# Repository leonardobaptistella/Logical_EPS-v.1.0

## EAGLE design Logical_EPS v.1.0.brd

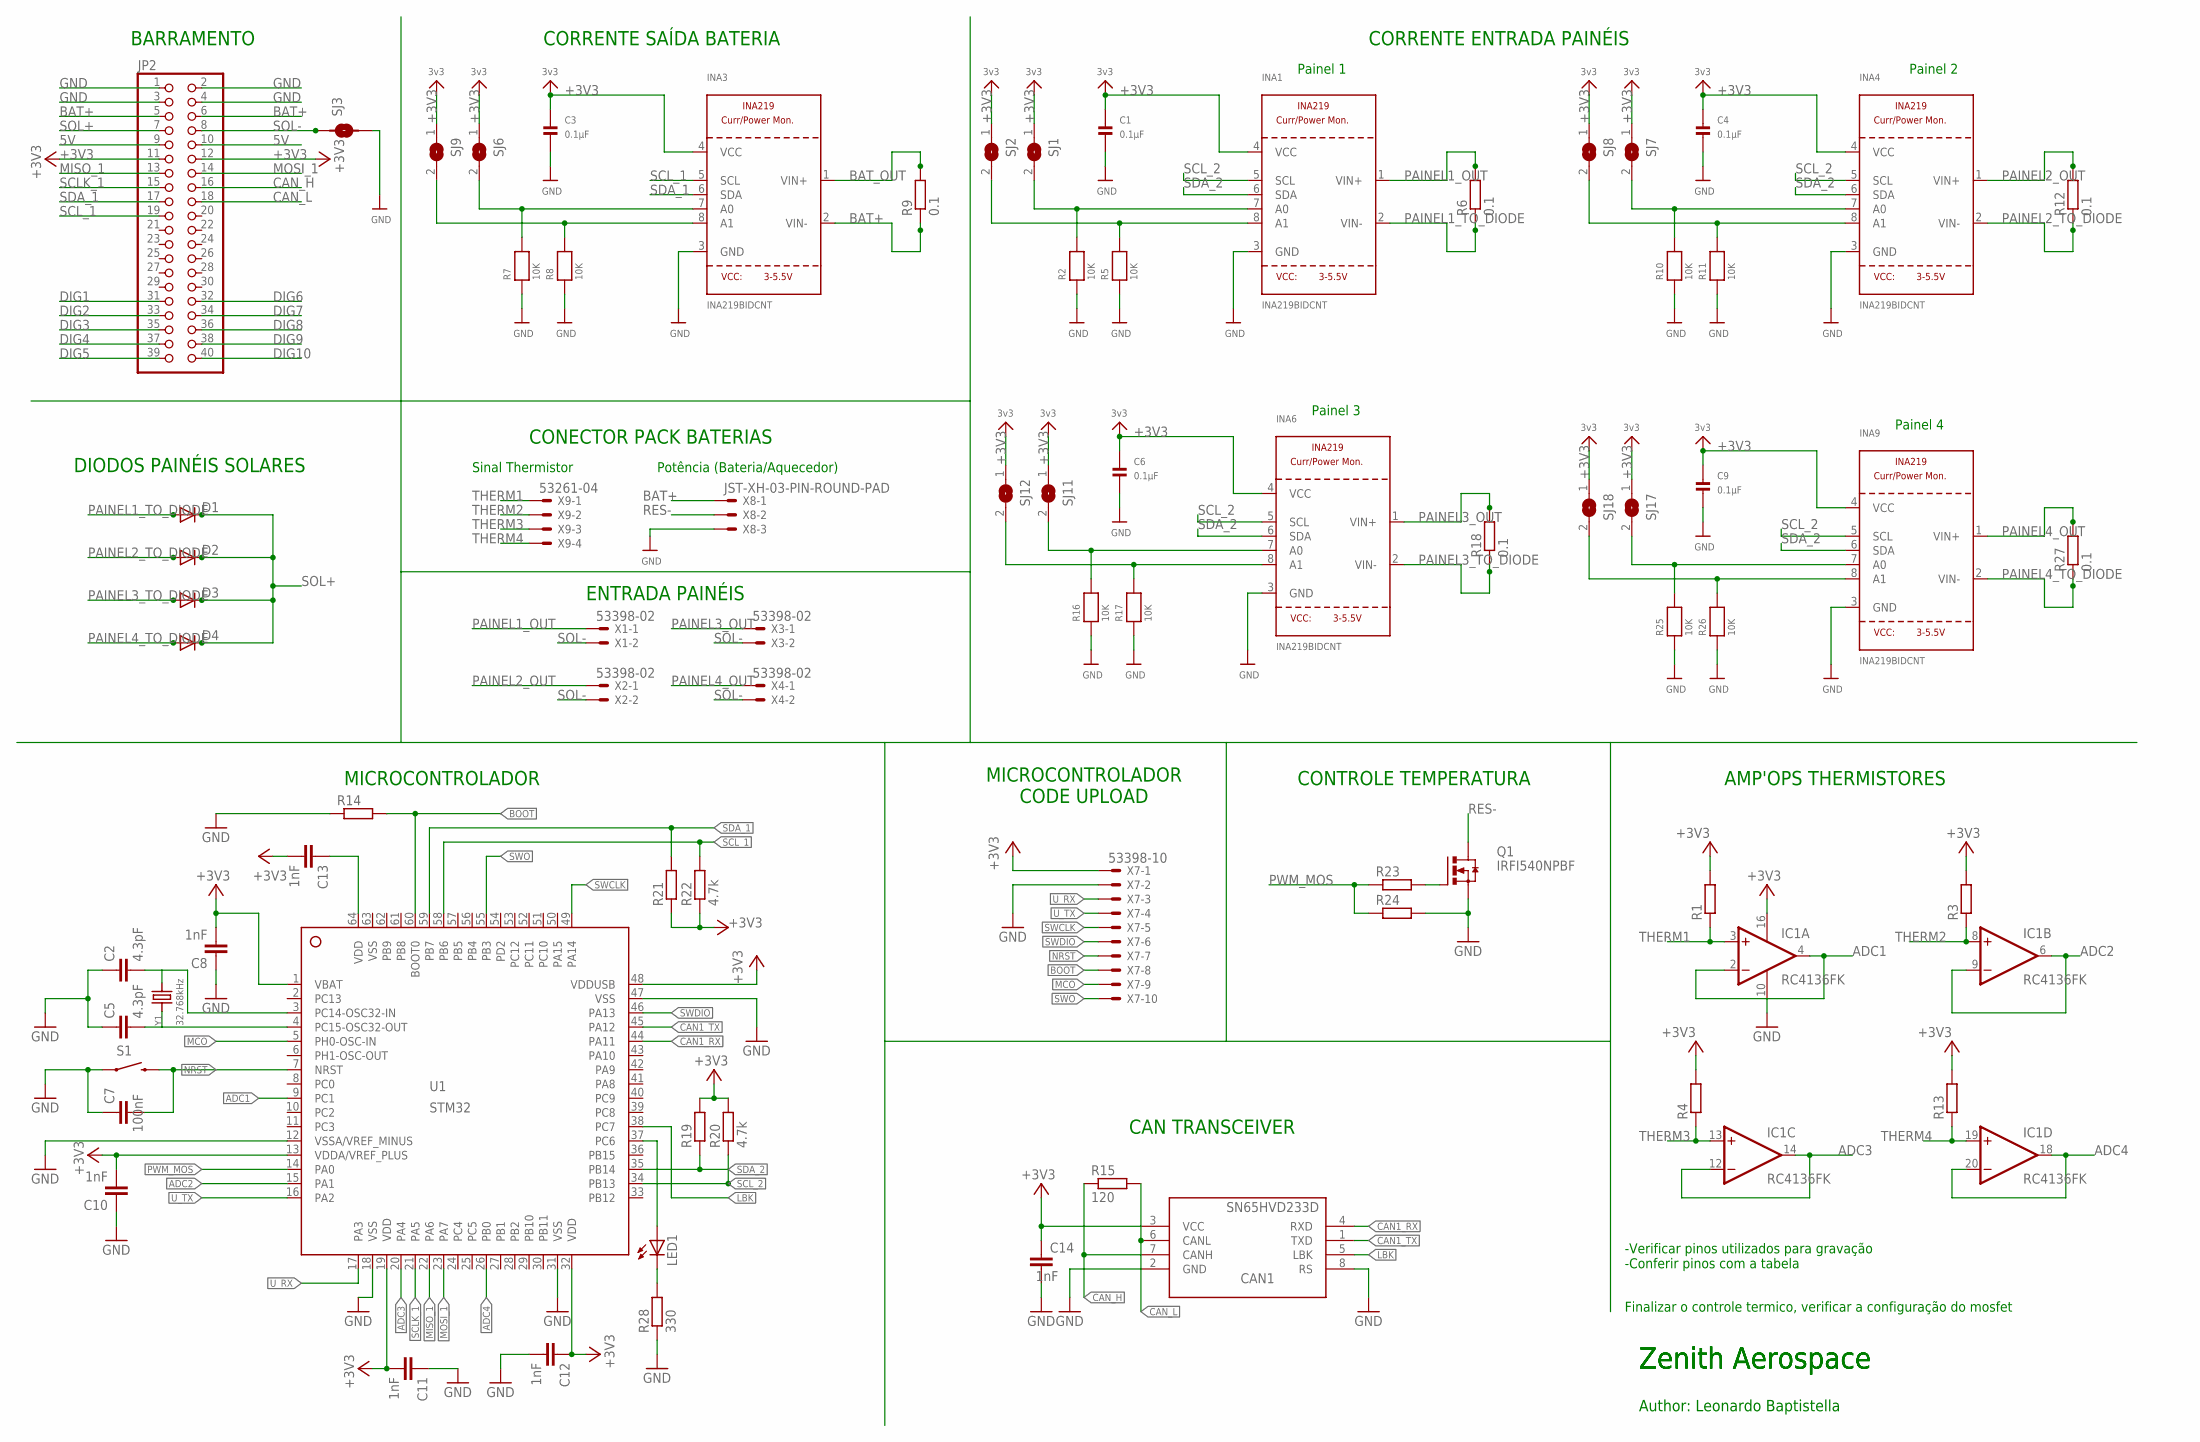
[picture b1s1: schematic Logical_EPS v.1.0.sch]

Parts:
C1, C3, C4, C6, C9: 0.1µF; 1206
C2, C5: 4.3pF; C1206
C7: 100nF; C1206
C8, C10, C11, C12, C13, C14: 1nF; C1206
CAN1: SN65HVD233D; SOIC8
D1, D2, D3, D4: DIODE-DO-214AC; DO-214AC
IC1: RC4136FK; PLCC20S
INA1, INA3, INA4, INA6, INA9: INA219BIDCNT; SOT23-8
JP2: PINHD-2X20; 2X20
LED1: LEDSMT1206; 1206
Q1: IRFI540NPBF; TO220BH
R1, R3, R4, R13, R14, R23, R24: R-EU_R1206; R1206
R2, R5, R7, R8, R10, R11, R16, R17, R25, R26: 10K; 1206
R6, R9, R12, R18, R27: 0.1; R2512
R15: 120; R1206
R19, R20, R21, R22: 4.7k; R1206
R28: 330; R1206
S1: SWITCH-MOMENTARY-2SMD-1101NE; TACTILE-SWITCH-1101NE
SJ1, SJ2, SJ6, SJ7, SJ8, SJ9, SJ11, SJ12, SJ17, SJ18: SOLDERJUMPERREFLOW_NOPASTE; SOLDERJUMPER_REFLOW_NOPASTE
SJ3: SMD-JUMPER-2
U1: STM32; LQFP64_10X10
X1, X2, X3, X4: 53398-02
X7: 53398-10
X8: JST-XH-03-PIN-ROUND-PAD; JST-XH-03-PACKAGE-ROUND-PAD
X9: 53261-04
Y1: 32.768kHz; CRYSTAL_8X3.8

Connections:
5V: JP2.9, JP2.10
+3V3: C1.1, C3.1, C4.1, C6.1, C8.2, C9.1, C10.2, C11.2, C12.1, C13.2, C14.1, CAN1.3 (VCC), IC1.16 (V+), INA1.4 (VCC), INA3.4 (VCC), INA4.4 (VCC), INA6.4 (VCC), INA9.4 (VCC), JP2.11, JP2.12, R1.2, R3.2, R4.2, R13.2, R19.2, R20.2, R21.1, R22.1, SJ1.1, SJ2.1, SJ6.1, SJ7.1, SJ8.1, SJ9.1, SJ11.1, SJ12.1, SJ17.1, SJ18.1, U1.1 (VBAT), U1.13 (VDDA/VREF_PLUS), U1.19 (VDD), U1.32 (VDD), U1.48 (VDDUSB), X7.1
ADC1: IC1.2 (-IN), IC1.4 (OUT), U1.9 (PC1)
ADC2: IC1.6 (OUT), IC1.9 (-IN), U1.15 (PA1)
ADC3: IC1.12 (-IN), IC1.14 (OUT), U1.20 (PA4)
ADC4: IC1.18 (OUT), IC1.20 (-IN), U1.26 (PB0)
BAT+: INA3.2 (VIN-), JP2.5, JP2.6, R9.1, X8.1
BAT_OUT: INA3.1 (VIN+), R9.2
BOOT: R14.2, U1.60 (BOOT0), X7.8
CAN1_RX: CAN1.4 (RXD), U1.44 (PA11)
CAN1_TX: CAN1.1 (TXD), U1.45 (PA12)
CAN_H: CAN1.7 (CANH), JP2.16, R15.1
CAN_L: CAN1.6 (CANL), JP2.18, R15.2
DIG1: JP2.31
DIG2: JP2.33
DIG3: JP2.35
DIG4: JP2.37
DIG5: JP2.39
DIG6: JP2.32
DIG7: JP2.34
DIG8: JP2.36
DIG9: JP2.38
DIG10: JP2.40
GND: C1.2, C2.1, C3.2, C4.2, C5.1, C6.2, C7.1, C8.1, C9.2, C10.1, C11.1, C12.2, C14.2, CAN1.2 (GND), CAN1.8 (RS), IC1.10 (V-), INA1.3 (GND), INA3.3 (GND), INA4.3 (GND), INA6.3 (GND), INA9.3 (GND), JP2.1, JP2.2, JP2.3, JP2.4, Q1.S, R2.1, R5.1, R7.1, R8.1, R10.1, R11.1, R14.1, R16.1, R17.1, R24.2, R25.1, R26.1, R28.1, S1.1, SJ3.2, U1.12 (VSSA/VREF_MINUS), U1.18 (VSS), U1.31 (VSS), U1.47 (VSS), X7.2, X8.3
LBK: CAN1.5 (LBK), U1.38 (PC7)
MCO: U1.5 (PH0-OSC-IN), X7.9
MISO_1: JP2.13, U1.22 (PA6)
MOSI_1: JP2.14, U1.23 (PA7)
unnamed: C2.2, U1.3 (PC14-OSC32-IN), Y1.P$4 (2)
unnamed: Q1.G, R23.2
unnamed: C5.2, U1.4 (PC15-OSC32-OUT), Y1.P$1 (1)
unnamed: C13.1, U1.64 (VDD)
unnamed: INA1.8 (A1), R5.2, SJ2.2
unnamed: INA1.7 (A0), R2.2, SJ1.2
unnamed: INA3.8 (A1), R8.2, SJ9.2
unnamed: INA3.7 (A0), R7.2, SJ6.2
unnamed: INA4.8 (A1), R11.2, SJ8.2
unnamed: INA4.7 (A0), R10.2, SJ7.2
unnamed: LED1.A, U1.37 (PC6)
unnamed: LED1.C, R28.2
unnamed: INA6.8 (A1), R17.2, SJ12.2
unnamed: INA6.7 (A0), R16.2, SJ11.2
unnamed: INA9.8 (A1), R26.2, SJ18.2
unnamed: INA9.7 (A0), R25.2, SJ17.2
NRST: C7.2, S1.2, U1.7 (NRST), X7.7
PAINEL1_OUT: INA1.1 (VIN+), R6.2, X1.1
PAINEL1_TO_DIODE: D1.A, INA1.2 (VIN-), R6.1
PAINEL2_OUT: INA4.1 (VIN+), R12.2, X2.1
PAINEL2_TO_DIODE: D2.A, INA4.2 (VIN-), R12.1
PAINEL3_OUT: INA6.1 (VIN+), R18.2, X3.1
PAINEL3_TO_DIODE: D3.A, INA6.2 (VIN-), R18.1
PAINEL4_OUT: INA9.1 (VIN+), R27.2, X4.1
PAINEL4_TO_DIODE: D4.A, INA9.2 (VIN-), R27.1
PWM_MOS: R23.1, R24.1, U1.14 (PA0)
RES-: Q1.D, X8.2
SCLK_1: JP2.15, U1.21 (PA5)
SCL_1: INA3.5 (SCL), JP2.19, R22.2, U1.58 (PB6)
SCL_2: INA1.5 (SCL), INA4.5 (SCL), INA6.5 (SCL), INA9.5 (SCL), R20.1, U1.34 (PB13)
SDA_1: INA3.6 (SDA), JP2.17, R21.2, U1.59 (PB7)
SDA_2: INA1.6 (SDA), INA4.6 (SDA), INA6.6 (SDA), INA9.6 (SDA), R19.1, U1.35 (PB14)
SOL+: D1.C, D2.C, D3.C, D4.C, JP2.7
SOL-: JP2.8, SJ3.1, X1.2, X2.2, X3.2, X4.2
SWCLK: U1.49 (PA14), X7.5
SWDIO: U1.46 (PA13), X7.6
SWO: U1.55 (PB3), X7.10
THERM1: IC1.3 (+IN), R1.1, X9.1
THERM2: IC1.8 (+IN), R3.1, X9.2
THERM3: IC1.13 (+IN), R4.1, X9.3
THERM4: IC1.19 (+IN), R13.1, X9.4
U_RX: U1.17 (PA3), X7.3
U_TX: U1.16 (PA2), X7.4
VSS: U1.63 (VSS)

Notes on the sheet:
ENTRADA PAINÉIS
BARRAMENTO
CORRENTE ENTRADA PAINÉIS
CORRENTE SAÍDA BATERIA
Painel 1
Painel 2
Painel 3
Painel 4
DIODOS PAINÉIS SOLARES
CONECTOR PACK BATERIAS
Sinal Thermistor
Potência (Bateria/Aquecedor)
AMP'OPS THERMISTORES
CONTROLE TEMPERATURA
Finalizar o controle termico, verificar a configuração do mosfet
Author: Leonardo Baptistella
Zenith Aerospace
-Verificar pinos utilizados para gravação -Conferir pinos com a tabela
MICROCONTROLADOR
MICROCONTROLADOR CODE UPLOAD
CAN TRANSCEIVER

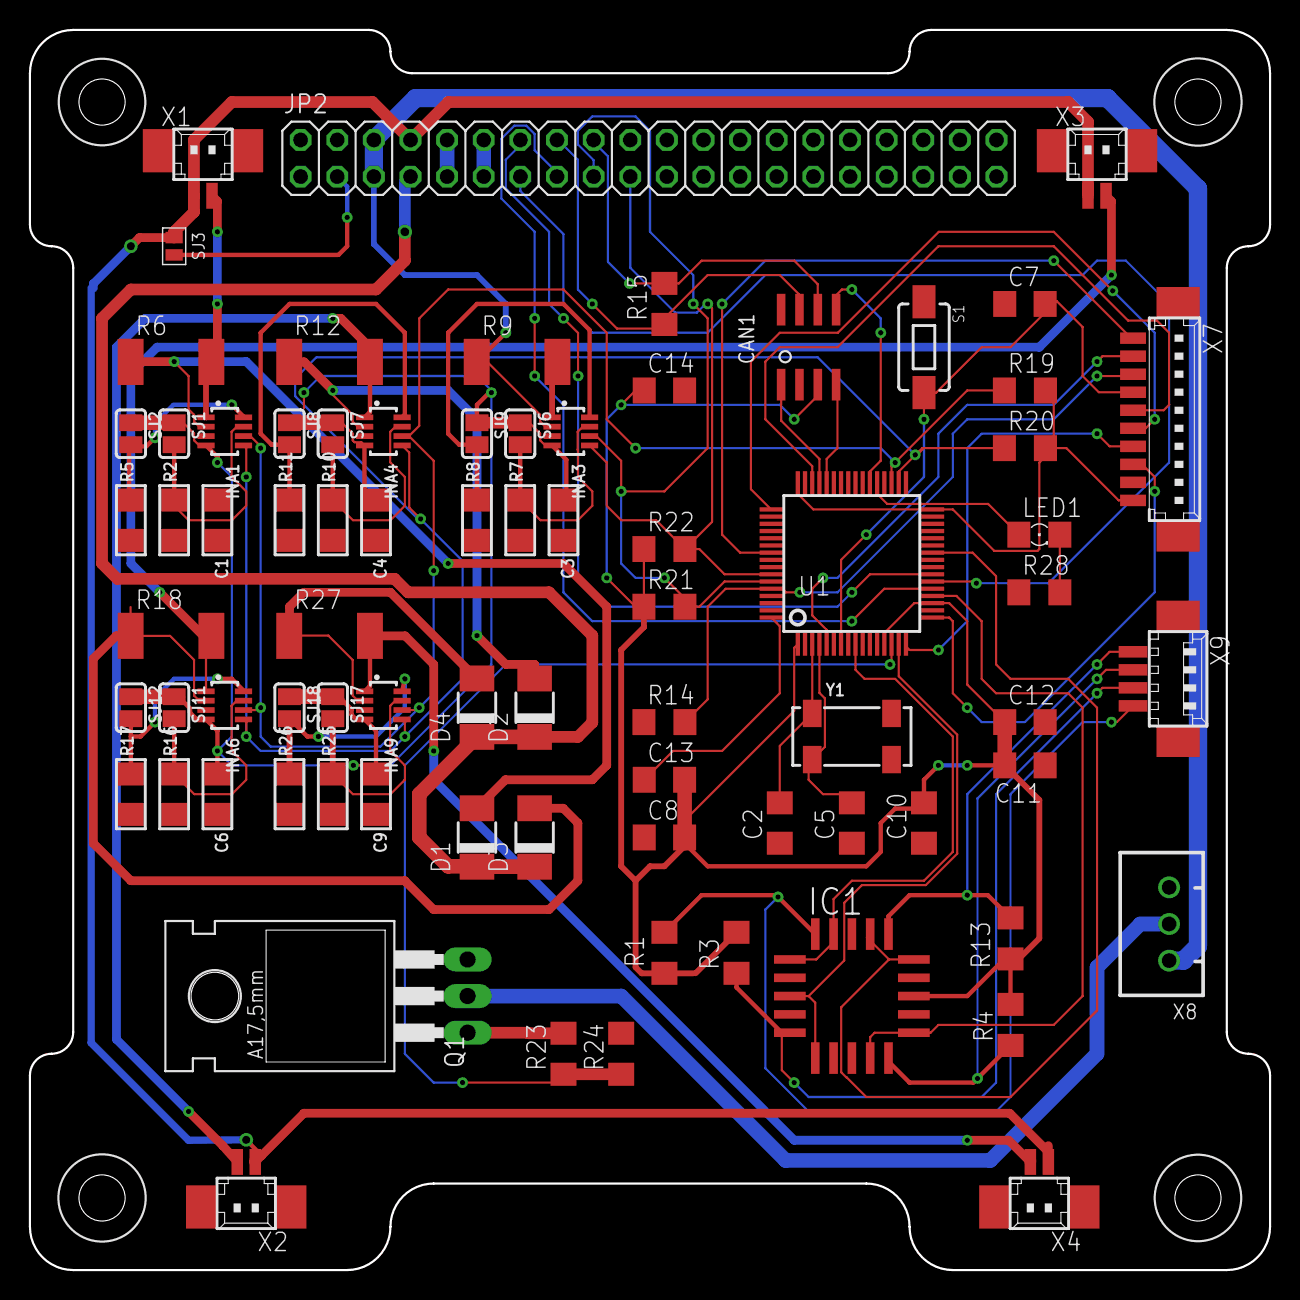
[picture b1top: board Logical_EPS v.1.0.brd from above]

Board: 2 copper layers, 86.0 x 86.0 mm, 77 parts (0 on the bottom side), 61 nets.

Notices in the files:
parts and their libraries:
FaBo-etc: Released under the Creative Commons Attribution-ShareAlike 4.0 License
https://creativecommons.org/licenses/by-sa/4.0
SparkFun-Electromechanical: Licensing: Creative Commons ShareAlike 4.0 International - https://creativecommons.org/licenses/by-sa/4.0
